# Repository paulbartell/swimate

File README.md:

swimate
=======

SwiMate, a device for tracking your movements while swimming.

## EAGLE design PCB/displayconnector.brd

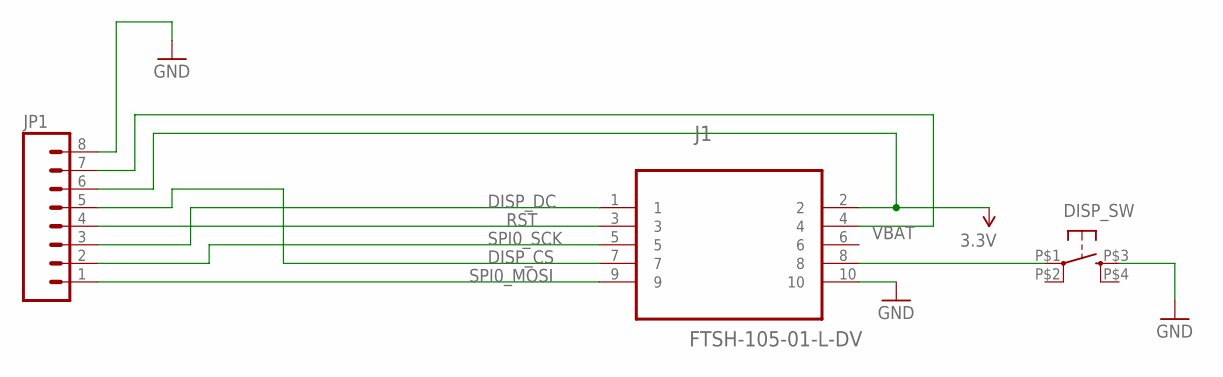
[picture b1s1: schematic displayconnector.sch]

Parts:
DISP_SW: TAC_SWITCHKSA_SEALED; KSA_SEALED_TAC_SWITCH
J1: FTSH-105-01-L-DV; SAMTEC_FTSH-105-01-L-DV
JP1: M08LOCK_LONGPADS; 1X08_LOCK_LONGPADS

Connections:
3.3V: J1.2, JP1.6
DISP_CS: J1.7, JP1.5
DISP_DC: J1.1, JP1.3
DISP_SW: DISP_SW.P$1 (1), J1.8
GND: DISP_SW.P$3 (3), J1.10, JP1.8
RST: J1.3, JP1.4
SPI0_MOSI: J1.9, JP1.1
SPI0_SCK: J1.5, JP1.2
VBAT: J1.4, JP1.7

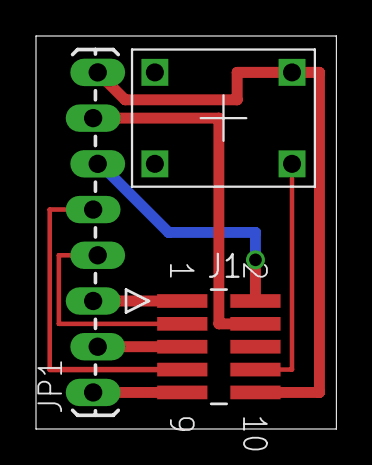
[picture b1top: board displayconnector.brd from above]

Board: 2 copper layers, 16.7 x 21.8 mm, 3 parts (0 on the bottom side), 9 nets.

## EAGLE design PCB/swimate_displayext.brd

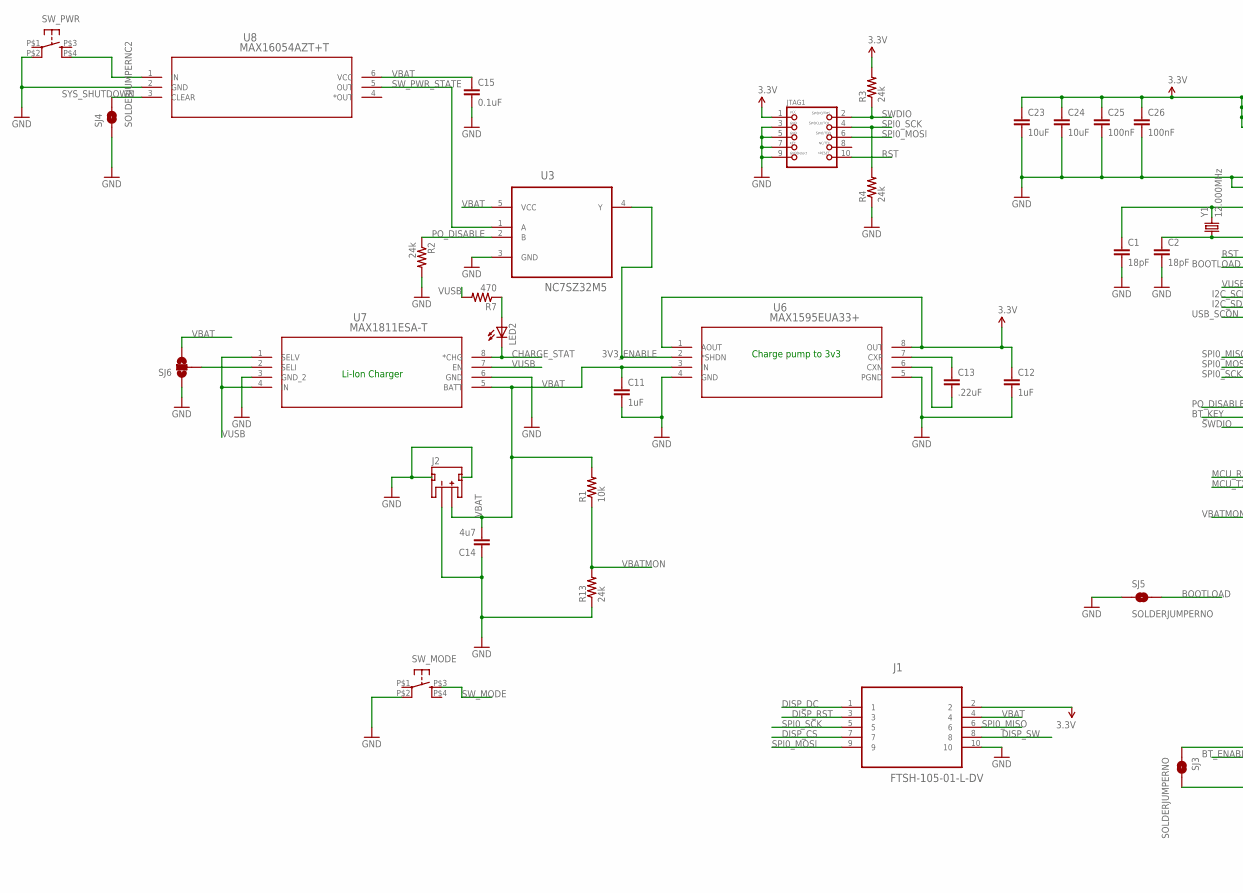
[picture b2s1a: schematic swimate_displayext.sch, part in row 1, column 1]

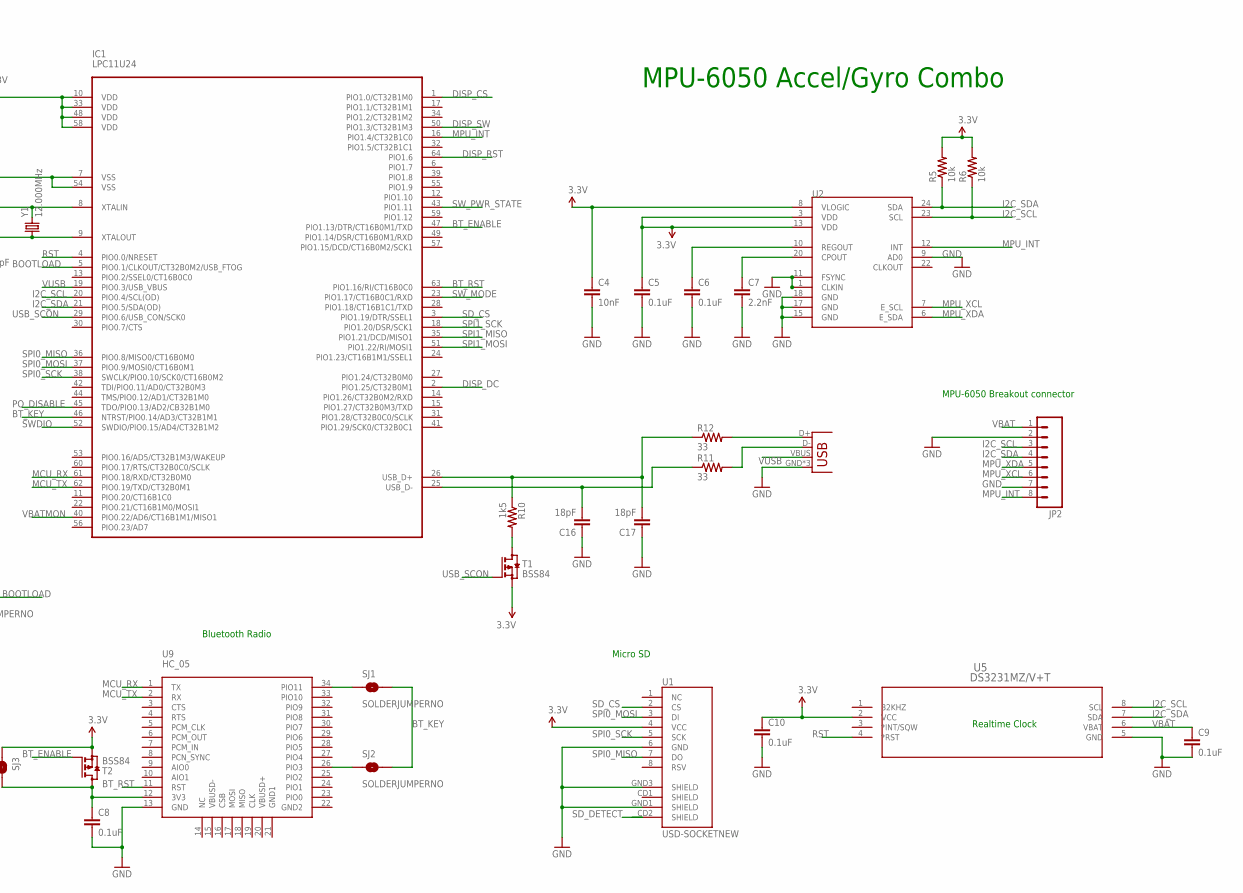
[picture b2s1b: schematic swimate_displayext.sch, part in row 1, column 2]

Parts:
C1, C2, C16, C17: 18pF; 0805
C4: 10nF; 0805
C5, C6, C8, C9, C10, C15: 0.1uF; 0805
C7: 2.2nF; 0805
C11, C12: 1uF; 1206
C13: .22uF; 0805
C14: 4u7; 1206
C23, C24: 10uF; 0805
C25, C26: 100nF; 0805
IC1: LPC11U24; MBED-ICS_LQFP64
J1: FTSH-105-01-L-DV; SAMTEC_FTSH-105-01-L-DV
J2: JST_2MM_MALE; JST-2-SMD
JP2: M08; 1X08_PIN1_NO_SILK
JP3: USB-MICROB
JTAG1: JTAG-CORTEXM3; 2X05_1.27MM_SMT
LED2: LED0603; LED-0603
R1: 10k; 0603-RES
R2, R3, R4: 24k; 0805
R5, R6: 10k; 0805
R7: 470; 0805
R10: 1k5; 0805
R11, R12: 33; 0805
R13: 24k; 0603-RES
SJ1, SJ2, SJ3, SJ5: SOLDERJUMPERNO; SJ_2S-NO
SJ4: SOLDERJUMPERNC2; SJ_2S-NOTRACE
SJ6: SOLDERJUMPER_2WAYS; SJ_3
SW_MODE: TAC_SWITCHKSA_SEALED; KSA_SEALED_TAC_SWITCH
SW_PWR: TAC_SWITCHKSA_SEALED; KSA_SEALED_TAC_SWITCH
T1, T2: BSS84; SOT23
U1: USD-SOCKETNEW; MICRO-SD-SOCKET-PP
U2: MPU-9150QFN-24-NP; QFN-24-NP
U3: NC7SZ32M5; SOT95P280X145-5N
U5: DS3231MZ/V+T; 21-0041B_8
U6: MAX1595EUA33+; 21-0036K
U7: MAX1811ESA-T; 21-0041B_8
U8: MAX16054AZT+T; 21-0114C
U9: HC_05; BLUETOOTH_SMD
Y1: 12.000MHz; CRYSTAL-SMD-10.5X4.8-2PIN

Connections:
3.3V: C4.1, C5.1, C10.1, C12.1, C23.1, C24.1, C25.1, C26.1, IC1.10 (VDD), IC1.33 (VDD), IC1.48 (VDD), IC1.58 (VDD), J1.2, JTAG1.1, R3.2, R5.2, R6.2, SJ3.1, T1.2 (S), T2.2 (S), U1.4 (VCC), U2.3 (VDD), U2.8 (VLOGIC), U2.13 (VDD), U5.2 (VCC), U6.1 (AOUT), U6.8 (OUT)
3V3_ENABLE: U3.4 (Y), U6.2 (*SHDN)
BOOTLOAD: IC1.5 (PIO0.1/CLKOUT/CT32B0M2/USB_FTOG), SJ5.2
BT_ENABLE: IC1.47 (PIO1.13/DTR/CT16B0M1/TXD), T2.1 (G)
BT_KEY: IC1.46 (NTRST/PIO0.14/AD3/CT32B1M1), SJ1.2, SJ2.2
BT_RST: IC1.63 (PIO1.16/RI/CT16B0C0), U9.11 (RST)
CHARGE_STAT: LED2.C, U7.8 (*CHG)
DISP_CS: IC1.1 (PIO1.0/CT32B1M0), J1.7
DISP_DC: IC1.2 (PIO1.25/CT32B0M1), J1.1
DISP_RST: IC1.64 (PIO1.6), J1.3
DISP_SW: IC1.50 (PIO1.3/CT32B1M3), J1.8
GND: C1.2, C2.2, C4.2, C5.2, C6.2, C7.2, C8.2, C9.2, C10.2, C11.2, C12.2, C14.1, C15.2, C16.1, C17.1, C23.2, C24.2, C25.2, C26.2, IC1.7 (VSS), IC1.54 (VSS), J1.10, J2.1 (-), J2.NC1 (PAD1), J2.NC2 (PAD2), JP2.2, JP2.7, JP3.GND, JP3.MT1 (GND), JP3.MT2 (GND), JTAG1.3, JTAG1.5, JTAG1.7, JTAG1.9, R2.2, R4.1, R13.1, SJ4.1, SJ5.1, SJ6.1, SW_MODE.P$2 (2), SW_PWR.P$2 (2), U1.6 (GND), U1.GND1 (SHIELD), U1.GND3 (SHIELD), U2.1 (CLKIN), U2.9 (AD0), U2.11 (FSYNC), U2.15 (GND), U2.17 (GND), U2.18 (GND), U3.3 (GND), U5.5 (GND), U6.4 (GND), U6.5 (PGND), U7.3 (GND_2), U7.6 (GND), U8.2 (GND), U9.13 (GND)
I2C_SCL: IC1.20 (PIO0.4/SCL(OD)), JP2.3, R6.1, U2.23 (SCL), U5.8 (SCL)
I2C_SDA: IC1.21 (PIO0.5/SDA(OD)), JP2.4, R5.1, U2.24 (SDA), U5.7 (SDA)
MCU_RX: IC1.61 (PIO0.18/RXD/CT32B0M0), U9.1 (TX)
MCU_TX: IC1.62 (PIO0.19/TXD/CT32B0M1), U9.2 (RX)
MPU_INT: IC1.16 (PIO1.4/CT32B1C0), JP2.8, U2.12 (INT)
MPU_XCL: JP2.6, U2.7 (E_SCL)
MPU_XDA: JP2.5, U2.6 (E_SDA)
unnamed: SW_PWR.P$4 (4), U8.1 (IN)
unnamed: SJ6.2, U7.2 (SELI)
unnamed: C6.1, U2.10 (REGOUT)
unnamed: C7.1, U2.20 (CPOUT)
unnamed: LED2.A, R7.1
unnamed: SJ2.1, U9.26 (PIO3)
unnamed: SJ1.1, U9.34 (PIO11)
unnamed: C13.1, U6.7 (CXP)
unnamed: C13.2, U6.6 (CXN)
unnamed: C8.1, SJ3.2, T2.3 (D), U9.12 (3V3)
unnamed: R10.2, T1.3 (D)
unnamed: JP3.D+, R12.2
unnamed: JP3.D-, R11.2
unnamed: C1.1, IC1.8 (XTALIN), Y1.P$2 (2)
unnamed: C2.1, IC1.9 (XTALOUT), Y1.P$1 (1)
PO_DISABLE: IC1.45 (TDO/PIO0.13/AD2/CB32B1M0), R2.1, U3.2 (B)
RST: IC1.4 (PIO0.0/NRESET), JTAG1.10, U5.4 (*RST)
SD_CS: IC1.3 (PIO1.19/DTR/SSEL1), U1.2 (CS)
SD_DETECT: U1.CD2 (SHIELD)
SPI0_MISO: IC1.36 (PIO0.8/MISO0/CT16B0M0), J1.6, U1.7 (DO)
SPI0_MOSI: IC1.37 (PIO0.9/MOSI0/CT16B0M1), J1.9, JTAG1.6, U1.3 (DI)
SPI0_SCK: IC1.38 (SWCLK/PIO0.10/SCK0/CT16B0M2), J1.5, JTAG1.4, R4.2, U1.5 (SCK)
SPI1_MISO: IC1.35 (PIO1.21/DCD/MISO1)
SPI1_MOSI: IC1.51 (PIO1.22/RI/MOSI1)
SPI1_SCK: IC1.18 (PIO1.20/DSR/SCK1)
SWDIO: IC1.52 (SWDIO/PIO0.15/AD4/CT32B1M2), JTAG1.2, R3.1
SW_MODE: IC1.23 (PIO1.17/CT16B0C1/RXD), SW_MODE.P$3 (3)
SW_PWR_STATE: IC1.43 (PIO1.11), U3.1 (A), U8.5 (OUT)
SYS_SHUTDOWN: SJ4.2, U8.3 (CLEAR)
USBD_N: C16.2, IC1.25 (USB_D-), R11.1
USBD_P: C17.2, IC1.26 (USB_D+), R10.1, R12.1
USB_SCON: IC1.29 (PIO0.6/USB_CON/SCK0), T1.1 (G)
VBAT: C9.1, C11.1, C14.2, C15.1, J1.4, J2.2 (+), JP2.1, R1.2, SJ6.3, U3.5 (VCC), U5.6 (VBAT), U6.3 (IN), U7.5 (BATT), U8.6 (VCC)
VBATMON: IC1.40 (PIO0.22/AD6/CT16B1M1/MISO1), R1.1, R13.2
VUSB: IC1.19 (PIO0.3/USB_VBUS), JP3.VBUS, R7.2, U7.1 (SELV), U7.4 (IN), U7.7 (EN)

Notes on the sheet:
MPU-6050 Accel/Gyro Combo
Micro SD
Realtime Clock
Bluetooth Radio
Charge pump to 3v3
MPU-6050 Breakout connector
Li-Ion Charger

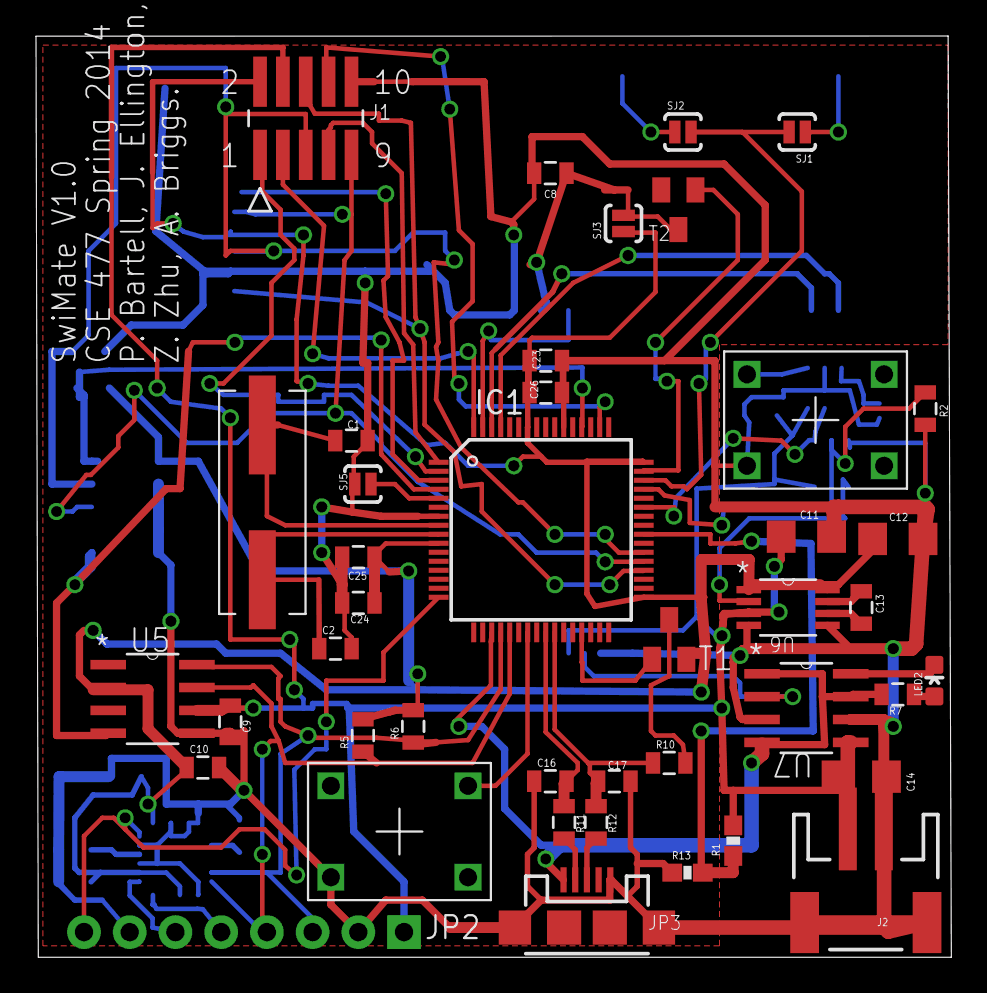
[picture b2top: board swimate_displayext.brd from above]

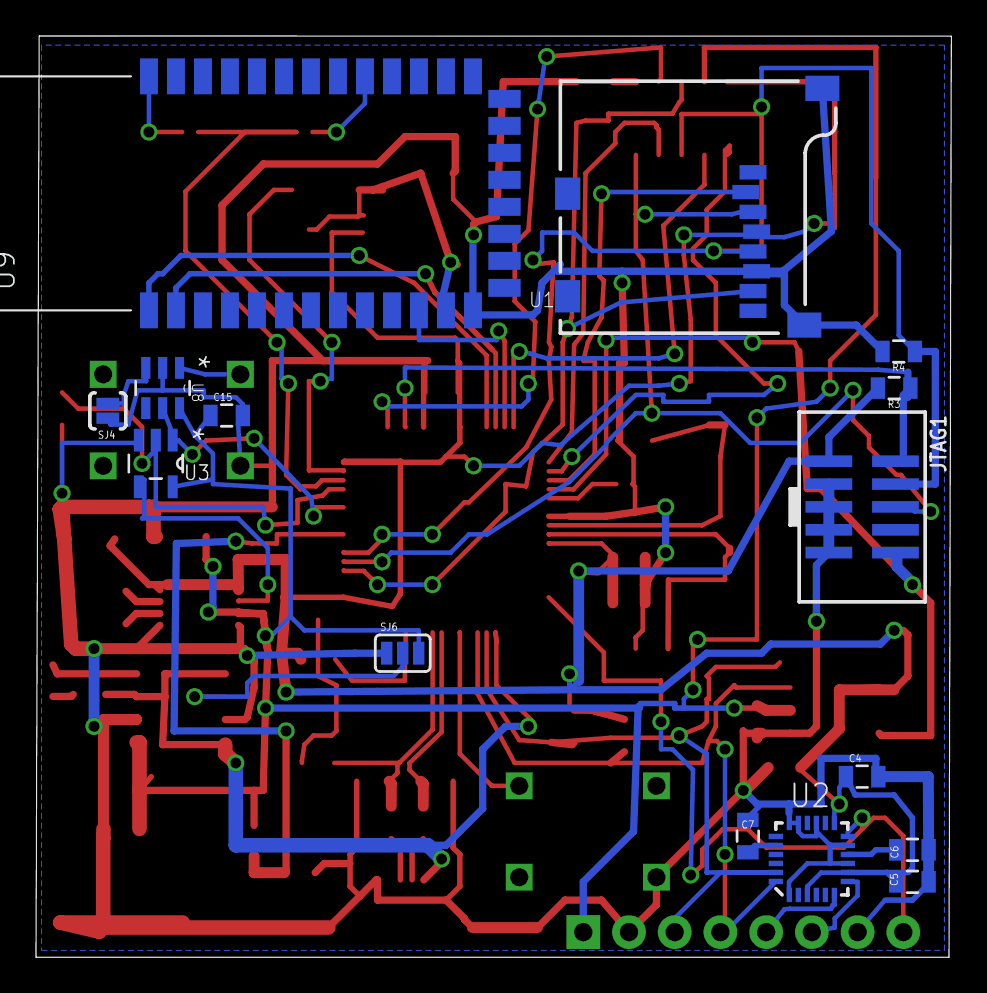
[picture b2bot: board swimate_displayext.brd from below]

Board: 2 copper layers, 50.9 x 51.2 mm, 57 parts (15 on the bottom side), 50 nets.

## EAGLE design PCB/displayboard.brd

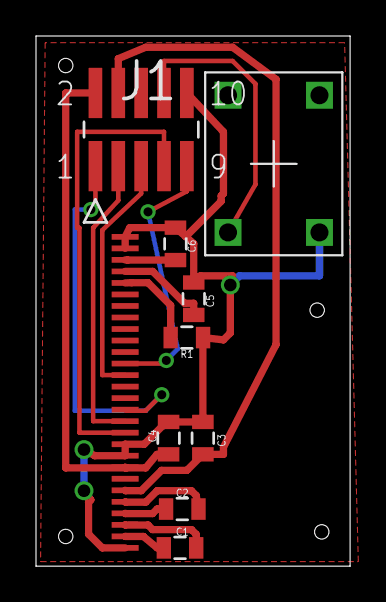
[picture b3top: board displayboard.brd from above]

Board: 2 copper layers, 17.4 x 29.5 mm, 10 parts (0 on the bottom side), 16 nets.

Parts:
C1, C2: 1uF; 0805
C3, C4: 2.2u; 0805
C5: 4.7uF; 0805
C6: 10uF; 0805
DISP_SW: KSA_SEALED_TAC_SWITCH
J1: FTSH-105-01-L-DV; SAMTEC_FTSH-105-01-L-DV
R1: 390K; 0805
U$1: UG-2864HSWEG01; 1X28-0.32MM

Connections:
3.3V: C4.2, J1.2, U$1.P$8
DISP_CS: J1.7, U$1.P$11
DISP_DC: J1.1, U$1.P$13
DISP_SW: DISP_SW.P$1, J1.8
GND: C3.1, C4.1, C5.1, C6.1, DISP_SW.P$3, J1.10, R1.1, U$1.P$1, U$1.P$7, U$1.P$9, U$1.P$10, U$1.P$27, U$1.P$28
unnamed: C2.1, U$1.P$5
unnamed: R1.2, U$1.P$24
unnamed: C1.2, U$1.P$2
unnamed: C6.2, U$1.P$26
unnamed: C1.1, U$1.P$3
unnamed: C5.2, U$1.P$25
unnamed: C2.2, U$1.P$4
RST: J1.3, U$1.P$12
SPI0_MOSI: J1.9, U$1.P$17
SPI0_SCK: J1.5, U$1.P$16
VBAT: C3.2, J1.4, U$1.P$6

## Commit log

2014-04-30 Started the PCB schematic
2014-05-01 Added SWD interface
2014-05-03 Charge pump added
2014-05-03 More improvements
    Added bluetooth disable circuit and various other parts.
2014-05-06 Added Display
2014-05-06 Added dispaly
2014-05-06 Starting Board layout.. still some pins to route
2014-05-06 More work on layout
2014-05-07 board update
2014-05-10 Working on the board
2014-05-14 changed pcb size and separated display portion
2014-05-15 Almost finished
2014-05-16 Passed DRC
    TODO: DRC, connect CS signals for display and SD card.
    TODO: replace connector for display board.
2014-05-16 Added PDF of schematic
2014-05-19 Added CS pins and turn off logic (MCU safe powerdown for SD card
2014-05-19 Displayboard completed.. Need to check connector width
2014-05-19 Moved connector onto page.
2014-05-19 display board update
2014-05-20 Added top and bottom ground and power planes
2014-05-20 added PDF version of schematic
2014-05-21 Final version of both PCBs.. Send to OSHPark
2014-05-21 Added display connector breakout / converter board
2014-05-21 added pdfs of schematics and board renderings
2014-05-29 Added pin list
2014-06-12 final backup from lab pc

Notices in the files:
parts and their libraries:
SparkFun-Capacitors: Licensing: Creative Commons ShareAlike 4.0 International - https://creativecommons.org/licenses/by-sa/4.0
microbuilder: This work is placed in the public domain, and may be freely used for commercial and non-commercial work with the following conditions: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
